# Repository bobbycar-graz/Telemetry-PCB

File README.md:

# Bobby-Car Telemetry PCB

This board should be mounted on the Bobby-Car.

There are 2 CAN bus connectors, pin-compatible with the boardcomputer PCB, and can either be wired:
- after the boardcomputer or
- in-line between the motorcontrollers and the boardcomputer

### Hardware Features
- SN65HVD230 CAN transceiver
- ESP32-WROOM-32E (8MB)
- CH343G USB to UART converter for programming
- ATGM336H-5N31 GNSS
  - supports GPS (US), GLONASS (Russia), Galileo (EU), BeiDou (China), QZSS (Japan)
  - u.FL connector for active antenna 
  - protocol compatible with NEO-6M
  - optional 3V rechargeable battery for fast cold start
- self bomb microSD card slot
- LM75B temperature sensor
- RA-01SH 868MHz LoRa module with two antenna options:
  - integrated u.FL connector for external helical antenna
  - solder jumper to enable the onboard PCB helical antenna
- TPMP2359DJ DC-DC converter (up to 30V input, 3.3V output), so board can be powered by:
  - USB-C connector (5V) or
  - CAN bus (12V-15V)
- TTL UART receive to receive log messages from the boardcomputer

### Use cases
- Acquire data with onboard sensors and send it to the boardcomputer
  - GPS/GNSS time, position, speed, heading
  - temperature
- Log data to the microSD card:
   - GPS and temperature data
   - CAN BUS messages
   - LoRa messages
   - ESP-NOW messages
   - GPS-mapped Wi-Fi scan results
   - UART log messages from the boardcomputer
- GPS geofencing (slowdown/stop, notification to other Bobby-Cars)
- Calibrate wheel circumference by comparing GPS speed with wheel speed
- Send GPS position over LoRa so that:
  - other Bobby-Cars can show nearby Bobby-Cars on a radar display
  - the Bobby-Car can be tracked on a map in case of loss or theft
- Control actuators such as door openers, lights, etc. over LoRa
- Receive LoRa messages from environmental sensors such as weather stations, air quality sensors, etc.
- Send ESP-NOW beacons with the current UTC time to other Bobby-Cars that lack a GNSS receiver
- Upload microSD card data to a cloud service automatically when connected to a Wi-Fi network

### Compliance
- Compliant with RED Directive 2014/53/EU (Radio Equipment Directive)
- Wi-Fi 2.4GHz 802.11b/g/n certified by Wi-Fi Alliance
- FCC ID of ESP32-WROOM-32E: [2AC7Z-ESP32WROOM32E](https://fccid.io/2AC7Z-ESP32WROOM32E)
- Compliant with LVD Directive 2014/35/EU (Low Voltage Directive)
- Compliant with EMC standard EN 55032, EN 55024, EN 61000-6-2, EN 61000-6-4 (Class B)
- Compliant with RoHS Directive 2011/65/EU (Restriction of Hazardous Substances)
- Compliant with REACH Regulation (EC) No 1907/2006 (Registration, Evaluation, Authorisation and Restriction of Chemicals)
- Compliant with WEEE Directive 2012/19/EU (Waste Electrical and Electronic Equipment)
- Compliant with ELV Directive 2011/65/EU (End of Life Vehicle)
- Compliant with ISO 11898-1:2003 CAN bus physical layer and data link layer specifications

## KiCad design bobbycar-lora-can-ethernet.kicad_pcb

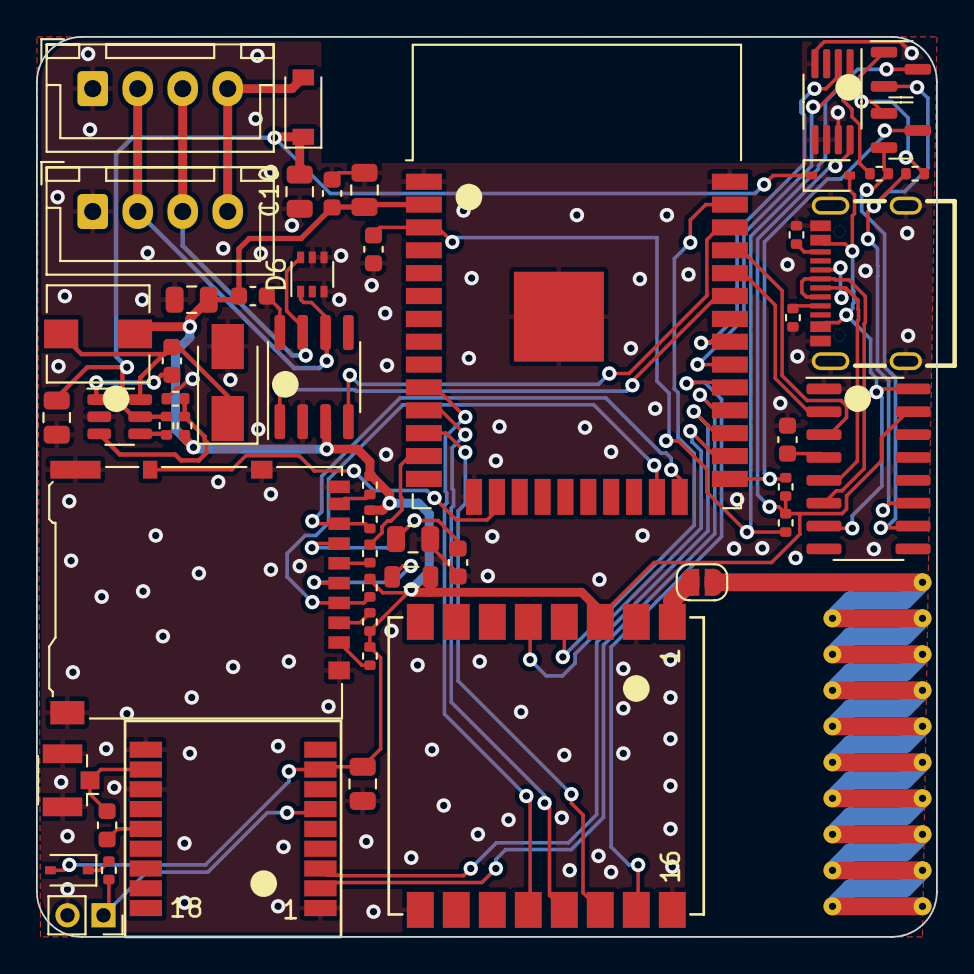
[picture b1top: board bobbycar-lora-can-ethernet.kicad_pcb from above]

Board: 2 copper layers, 50.0 x 50.0 mm, 53 parts (0 on the bottom side), 52 nets.

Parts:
AE1: Antenna_Shield; U.FL_Hirose_U.FL-R-SMT-1_Vertical
AE2: Antenna; Texas_SWRA416_868MHz_915MHz
BT1: Battery_Cell; PinSocket_1x02_P2.00mm_Vertical
C1, C7, C9, C10, C12: 10uF; C_0805_2012Metric
C3, C5, C6, C8, C13: 100n; C_0603_1608Metric
C4: 10u; C_0805_2012Metric
C11: 10n; C_0603_1608Metric
D1, D2: D_Schottky; D_SOD-323
D3: D; D_SOD-123
D4: B230A; D_SMA
D6: SP0505BAJT; SOT-363_SC-70-6
J1, J2: Conn_01x04; JST_XH_B4B-XH-A_1x04_P2.50mm_Vertical
J3: ATGM336H-5N31
J4: Micro_SD_Card_Det_Hirose_DM3AT; microSD_HC_Hirose_DM3AT-SF-PEJM5
JP1: Jumper_2_Open; SolderJumper-2_P1.3mm_Open_RoundedPad1.0x1.5mm
L1: 6.8nH; L_0603_1608Metric
L2: bead; L_0805_2012Metric
L3: 4.7uH; L_Wuerth_HCI-5040
Q1, Q2: SS8050_C2150; SOT-23
R1: 470; R_0402_1005Metric
R8, R12: 5k1; R_0402_1005Metric
R9, R10: 12k; R_0402_1005Metric
R13, R14: 10k; R_0402_1005Metric
R15: 1k; R_0402_1005Metric
R16, R17, R18, R19, R20, R21: 47k; R_0402_1005Metric
R24: 75k; R_0402_1005Metric
R25: 24k; R_0402_1005Metric
U1: ESP32-WROOM-32E; ESP32-WROOM-32
U2: Ai-Thinker-Ra-01SH; Ai-Thinker-Ra-01-LoRa
U3: LM75B; MSOP-8_3x3mm_P0.65mm
U5: CH343G; SOIC-16_3.9x9.9mm_P1.27mm
U6: SN65HVD231; SOIC-8_3.9x4.9mm_P1.27mm
U7: MPM2359; SOT-23-6
USBC1: MC-311D; USB-C-SMD_MC-311D

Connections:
15V: C9.2, C10.2, D2.1 (K), D3.1 (K), R15.2, U7.5 (IN)
+3V3: C1.1, C4.2, C5.2, C8.1, C12.2, D1.2 (A), J3.8, L2.1, L3.2, R13.1, R14.2, R16.1, R17.1, R18.1, R20.1, R21.1, R24.2, U1.2 (VDD), U2.3 (VDD), U3.8 (+Vs), U5.15 (VIO), U6.3 (VCC)
+5V: D2.2 (A), U5.7 (VBUS), U5.16 (VDD5), USBC1.A4-B9 (VBUS), USBC1.B4-A9 (VBUS)
CANH: D6.6 (K), J1.3, J2.3, U6.7 (CANH)
CANL: D6.1 (K), J1.2, J2.2, U6.6 (CANL)
CAN_RX: U1.36 (IO22), U6.4 (R)
CAN_TX: U1.33 (IO21), U6.1 (D)
DTR: Q2.2 (E), R9.1, U5.10 (~DTR/TNOW)
EN: C13.2, Q1.3 (C), R13.2, U1.3 (EN)
ESP_RX: U1.34 (RXD0/IO3), U5.2 (TXD)
ESP_TX: U1.35 (TXD0/IO1), U5.3 (RXD)
GND: AE1.2 (Shield), BT1.2 (-), C1.2, C3.1, C4.1, C5.1, C6.1, C7.2, C8.2, C9.1, C10.1, C12.1, C13.1, D4.2 (A), D6.3 (K), D6.4 (K), D6.5 (K), J1.1, J2.1, J3.1, J3.10, J3.12, J4.9 (DET_B), J4.11 (SHIELD), R8.2, R12.1, R25.1, U1.1 (GND), U1.15 (GND), U1.38 (GND), U1.39 (GND), U2.2 (GND), U2.9 (GND), U2.16 (GND), U3.4 (GND), U3.5 (A2), U3.6 (A1), U3.7 (A0), U5.1 (GND), U6.2 (GND), U6.8 (Rs), U7.2 (GND), USBC1.1 (SHIELD), USBC1.2 (SHIELD), USBC1.3 (SHIELD), USBC1.4 (SHIELD), USBC1.A1-B12 (GND), USBC1.B1-A12 (GND)
GPIO2_SD_DAT0: J4.7 (DAT0), R20.2, U1.24 (IO2)
GPIO14_SD_CLK: R19.1, U1.13 (IO14)
GPIO15_SD_CMD: J4.3 (CMD), R18.2, U1.23 (IO15)
GPS_RX: J3.3, U1.27 (IO16)
GPS_TX: J3.2, U1.28 (IO17)
I2S_SCL: U1.31 (IO19), U3.2 (SCL)
I2S_SDA: U1.30 (IO18), U3.1 (SDA)
IO0: Q2.3 (C), R14.1, U1.25 (IO0)
LORA_CLK: U1.10 (IO25), U2.12 (SCK)
LORA_MISO: U1.11 (IO26), U2.13 (MISO)
LORA_MOSI: U1.12 (IO27), U2.14 (MOSI)
LORA_NSS: U1.29 (IO5), U2.15 (~NSS)
LORA_RESET: U1.37 (IO23), U2.4 (~RESET)
LORA_TX_EN: U1.26 (IO4), U2.5 (DIO0)
unnamed: AE1.1 (A), J3.11, L1.1
unnamed: AE2.1 (A), JP1.2 (B)
unnamed: C3.2, U5.4 (V3)
unnamed: C6.2, C7.1, J4.6 (VSS)
unnamed: C11.1, D4.1 (K), L3.1, U7.6 (SW)
unnamed: C11.2, U7.1 (BST)
unnamed: D1.1 (K), R1.1
unnamed: D3.2 (A), J1.4, J2.4
unnamed: J3.14, L1.2
unnamed: J4.1 (DAT2), R16.2
unnamed: J4.2 (DAT3/CD), R17.2
unnamed: J4.4 (VDD), L2.2
unnamed: J4.5 (CLK), R19.2
unnamed: J4.8 (DAT1), R21.2
unnamed: JP1.1 (A), U2.1 (ANT)
unnamed: Q1.1 (B), R9.2
unnamed: Q2.1 (B), R10.2
unnamed: R8.1, USBC1.A5 (CC1)
unnamed: R12.2, USBC1.B5 (CC2)
unnamed: R15.1, U7.4 (EN)
unnamed: R24.1, R25.2, U7.3 (FB)
RTS: Q1.2 (E), R10.1, U5.11 (~RTS)
SD_DETECT: J4.10 (DET_A), U1.16 (IO13)
USB_DN: U5.6 (UD-), USBC1.A7 (DN1), USBC1.B7 (DN2)
USB_DP: U5.5 (UD+), USBC1.A6 (DP1), USBC1.B6 (DP2)
VBAT_3V: BT1.1 (+), J3.6, R1.2

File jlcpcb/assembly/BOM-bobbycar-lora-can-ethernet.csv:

Comment,Designator,Footprint,LCSC
bead,L2,L_0805_2012Metric,C1017
Micro_SD_Card_Det_Hirose_DM3AT,J4,microSD_HC_Hirose_DM3AT-SF-PEJM5,C114218
SN65HVD231,U6,SOIC-8_3.9x4.9mm_P1.27mm,C12084
MC-311D,USBC1,USB-C-SMD_MC-311D,C136423
Conn_01x04,"J1,J2",JST_XH_B4B-XH-A_1x04_P2.50mm_Vertical,C144395
100n,"C13,C3,C5,C6,C8",C_0603_1608Metric,C14663
10uF,"C1,C12,C4,C7",C_0805_2012Metric,C15850
D_Schottky,"D1,D2",D_SOD-323,C191023
1k,R15,R_0402_1005Metric,C21190
SS8050_C2150,"Q1,Q2",SOT-23,C2150
B230A,D4,D_SMA,C22452
12k,"R10,R9",R_0402_1005Metric,C22790
75k,R24,R_0402_1005Metric,C23184
5k1,"R12,R8",R_0402_1005Metric,C23186
470,R1,R_0402_1005Metric,C25117
24k,R25,R_0402_1005Metric,C25769
47k,"R16,R17,R18,R19,R20,R21",R_0402_1005Metric,C25792
10k,"R13,R14",R_0402_1005Metric,C25804
Ai-Thinker-Ra-01SH,U2,Ai-Thinker-Ra-01-LoRa,C2764087
LM75B,U3,MSOP-8_3x3mm_P0.65mm,C2837470
CH343G,U5,SOIC-16_3.9x9.9mm_P1.27mm,C2844153
MPM2359,U7,SOT-23-6,C2959845
6.8nH,L1,L_0603_1608Metric,C316305
4.7uH,L3,L_Wuerth_HCI-5040,C354606
10uF,"C10,C9",C_0805_2012Metric,C440198
10n,C11,C_0603_1608Metric,C57112
ESP32-WROOM-32E,U1,ESP32-WROOM-32,C701342
D,D3,D_SOD-123,C8598
Antenna_Shield,AE1,U.FL_Hirose_U.FL-R-SMT-1_Vertical,C88374
ATGM336H-5N31,J3,ATGM336H-5N31,C90770
SP0505BAJT,D6,SOT-363_SC-70-6,SMF05CT1G
Battery_Cell,BT1,PinSocket_1x02_P2.00mm_Vertical,
Jumper_2_Open,JP1,SolderJumper-2_P1.3mm_Open_RoundedPad1.0x1.5mm,
Antenna,AE2,Texas_SWRA416_868MHz_915MHz,

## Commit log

2022-09-29 initial order on jlcpcb
2022-09-29 add image
2022-09-29 added annotations
2022-09-30 improve README, add component number in schematics
2022-09-30 update use cases
